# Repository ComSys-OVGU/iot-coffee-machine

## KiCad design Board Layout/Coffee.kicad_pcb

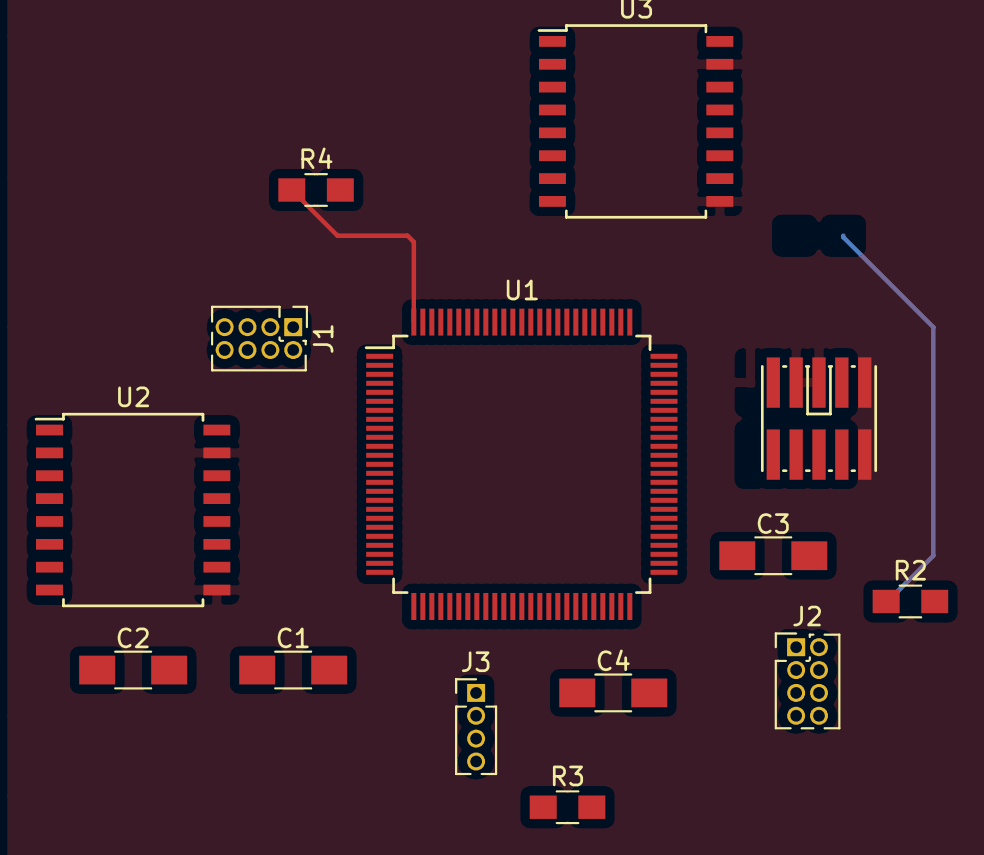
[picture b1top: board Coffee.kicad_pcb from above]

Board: 2 copper layers, 15 parts (1 on the bottom side), 29 nets.

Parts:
C1, C2, C3, C4: 0.1µ; C_1206_HandSoldering
CON1: AVR-JTAG-10; FTSH-105-XX-X-DV
J1, J2: Conn_02x04_Odd_Even; Pin_Header_Straight_2x04_Pitch1.27mm
J3: USART; Pin_Header_Straight_1x04_Pitch1.27mm
R1, R2, R3, R4: 10K; R_0805_HandSoldering
U1: STM32F407VGTx; LQFP-100_14x14mm_Pitch0.5mm
U2, U3: ISO7341FC; SOIC-16W_7.5x10.3mm_Pitch1.27mm

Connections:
+3V3: C1.1, C3.1, J3.4, R2.2, R4.1, U1.11, U1.19, U1.22, U1.28, U1.50, U1.75, U1.100, U2.1, U2.7, U3.1, U3.7
/LCD_MISO: J2.5, U3.11
/LCD_MOSI: J2.1, U3.14
/LCD_SCK: J2.3, U3.13
/NOCONN: U2.5, U2.12, U3.5
/NRST: CON1.10, U1.14
/PB_MISO: J1.5, U2.11
/PB_MOSI: J1.1, U2.14
/PB_SCK: J1.3, U2.13
/RXD0: J3.2, U1.26
/SPI1_MISO: U1.90, U2.6
/SPI1_MOSI: U1.91, U2.3
/SPI1_SCK: U1.89, U2.4
/SPI2_MISO: U1.53, U3.6
/SPI2_MOSI: U1.54, U3.3
/SPI2_SCK: U1.47, U3.4
/SWDCLK: CON1.4, U1.76
/SWDIO: CON1.2, U1.72
/SWDO: CON1.6, U1.95
/TXD0: J3.1, U1.25
Earth: C1.2, C3.2, J3.3, R1.1, R3.2, U1.10, U1.20, U1.27, U1.74, U1.99, U2.2, U2.8, U3.2, U3.8
GND: CON1.3, CON1.5, CON1.9, U2.9, U2.15, U3.9, U3.15
unnamed: C2.1, C4.1, J1.7, J2.7, U2.10, U2.16, U3.10, U3.16
unnamed: C2.2, C4.2, J1.8, J2.8
unnamed: J1.2, J2.2
unnamed: J1.4, J2.4
unnamed: J1.6, J2.6
unnamed: R1.2, R2.1, U1.94
unnamed: R3.1, R4.2, U1.37

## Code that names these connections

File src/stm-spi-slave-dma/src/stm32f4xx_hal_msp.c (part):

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    __HAL_RCC_SPI1_CLK_ENABLE();
  
    /**SPI1 GPIO Configuration    
    PB3     ------> SPI1_SCK
    PB4     ------> SPI1_MISO
    PB5     ------> SPI1_MOSI 
    */
    GPIO_InitStruct.Pin = GPIO_PIN_3|GPIO_PIN_4|GPIO_PIN_5;
    GPIO_InitStruct.Mode = GPIO_MODE_AF_PP;
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    __HAL_RCC_SPI2_CLK_ENABLE();
  
    /**SPI2 GPIO Configuration    
    PB13     ------> SPI2_SCK
    PB14     ------> SPI2_MISO
    PB15     ------> SPI2_MOSI 
    */
    GPIO_InitStruct.Pin = GPIO_PIN_13|GPIO_PIN_14|GPIO_PIN_15;
    GPIO_InitStruct.Mode = GPIO_MODE_AF_PP;
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    __HAL_RCC_SPI1_CLK_DISABLE();
  
    /**SPI1 GPIO Configuration    
    PB3     ------> SPI1_SCK
    PB4     ------> SPI1_MISO
    PB5     ------> SPI1_MOSI 
    */
    HAL_GPIO_DeInit(GPIOB, GPIO_PIN_3|GPIO_PIN_4|GPIO_PIN_5);

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    __HAL_RCC_SPI2_CLK_DISABLE();
  
    /**SPI2 GPIO Configuration    
    PB13     ------> SPI2_SCK
    PB14     ------> SPI2_MISO
    PB15     ------> SPI2_MOSI 
    */
    HAL_GPIO_DeInit(GPIOB, GPIO_PIN_13|GPIO_PIN_14|GPIO_PIN_15);

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
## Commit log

2017-10-19 initial version with working communication
2017-10-19 upgrade to cubemx generated project (should make it easier in the future), move code to lib
2017-10-19 proper testmode with uart feedback
2017-10-27 cleanup code for release
2017-10-27 move code to subdir for repo-consolidation
2017-10-27 add transform-js for decoding the logic analyzer csvs
2017-10-27 add protocol description
2017-10-27 add results
2017-11-11 move to src
2017-11-11 Add verbose error handler, keep working when cs was invalid
2017-11-11 add SPI1 for PB<->stm32 communication
    also, fix the clock-settings to have a solid 125KHz clock @SPI1
2017-11-12 current working state, basic proxy between PB and LCD is working
    timings are way off though, see images
2017-11-14 rename LEDs for better identification
2017-11-14 increase uart baudrate
2017-11-14 change the way checksums are handled
    instead of halting on cs-err, we now keep track of the # of times it happens and display it on uart.
2017-11-15 overhauled the way the statemachine works
    syncing is now part of the statemachine and so are the times in which communication is happening
2017-11-15 increase baudrate again for minimum transfer time
2017-11-15 remove wrongly merged button code
2017-11-15 wake PB from deep sleep
2017-11-15 began button interrupt implementation
2017-11-15 basic implementation of buttons
    this only emulates one button: the OK btn
2017-11-22 keynote
2017-11-23 snapshot of working state with md machine
2017-12-08 move v1 and v2 constants into different files; cleanup handler
2017-12-27 move includes to seperate directory, cleanup
2017-12-27 fix build errors by renaming includes directory
2017-12-29 first working version of UART handler
2017-12-30 implement DMA timeout with UART IDLE detection
2017-12-30 implement packet overwrite as well as masks
2018-01-04 implement logmasks to reduce log traffic
2018-01-04 first version of webinterface
2018-01-05 mobx working state
2018-01-06 Board Layout Kicad schematic file
2018-01-06 Coffee.sch
2018-01-06 Coffee-cache.lib
2018-01-06 Coffee-rescue.lib
2018-01-06 Coffee.pro
2018-01-06 Coffee.net
2018-01-06 Coffee.kicad_pcb
2018-01-06 Coffee.bak
2018-01-06 STM32 MCU Library
2018-01-08 data sheets for board
2018-01-09 implement control page + debug page
2018-01-10 add logging lib (which allows for unsolicited logs)
2018-01-21 implement PB log-filtering
2018-02-02 Upload New File
2018-03-08 add device-client, update firmware for new client, added more protocol bits and v2 protocol
2018-03-15 Replace Coffee-cache.lib
2018-03-15 Replace Coffee-rescue.lib
2018-03-15 Replace Coffee.bak
2018-03-15 Replace Coffee.kicad_pcb
2018-03-15 Replace Coffee.net
2018-03-15 Replace Coffee.pro
2018-03-15 Replace Coffee.sch
2018-03-21 added sqlite store, show actual history, allow for orders via http
2018-03-21 add verteidigungskeynote
2018-03-21 add fake transport for testing
2018-03-28 Added License

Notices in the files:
src/stm-spi-slave-dma/src/stm32f4xx_hal_msp.c:
COPYRIGHT(c) 2017 STMicroelectronics
(C) COPYRIGHT STMicroelectronics *****END OF FILE
